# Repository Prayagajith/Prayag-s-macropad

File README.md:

# Prayag's Macropad
### My wonderful macropad that can be used for anything like video editting, 3d modeling, and maybe even for streaming

BOM:
- 12x Cherry MX Switches
- 12x 1N4148 Diodes
- 1x SK6812 MINI Led
- 1x EC11 Rotary Encoder 
- 1x XIAO RP2040
- 12x Blank DSA Keycaps
- 4x M3x16 Bolt
- 4x M3 Heatset

Schematic            |  PCB         |   Case
:-------------------------:|:-------------------------:|:-------------------------:|
 |  | 

## Extra Stuff

Had no idea what I was doing at the start but learnt along the way and learning new interesting stuff is always fun so had a lot of fun designing this project even though it is simple

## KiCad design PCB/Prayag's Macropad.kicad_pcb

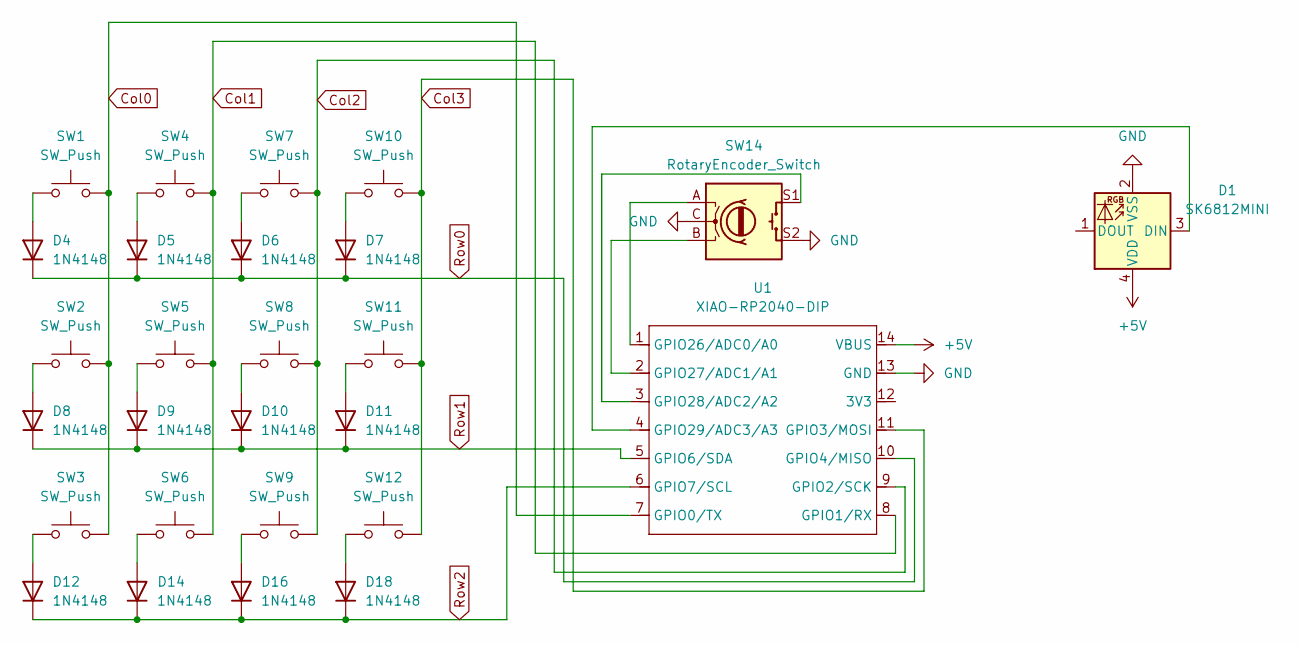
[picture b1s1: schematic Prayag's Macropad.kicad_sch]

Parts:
D1: SK6812MINI; LED_SK6812MINI_PLCC4_3.5x3.5mm_P1.75mm
D4, D5, D6, D7, D8, D9, D10, D11, D12, D14, D16, D18: 1N4148; D_DO-35_SOD27_P7.62mm_Horizontal
SW1, SW2, SW3, SW4, SW5, SW6, SW7, SW8, SW9, SW10, SW11, SW12: SW_Push; SW_Cherry_MX_1.00u_PCB
SW14: RotaryEncoder_Switch; RotaryEncoder_Alps_EC11E-Switch_Vertical_H20mm
U1: XIAO-RP2040-DIP

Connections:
+5V: D1.4 (VDD), U1.14 (VBUS)
Col0: SW1.2, SW2.2, SW3.2, U1.7 (GPIO0/TX)
Col1: SW4.1, SW5.1, SW6.1, U1.8 (GPIO1/RX)
Col2: SW7.1, SW8.1, SW9.1, U1.9 (GPIO2/SCK)
Col3: SW10.2, SW11.2, SW12.2, U1.11 (GPIO3/MOSI)
GND: D1.2 (VSS), SW14.C, SW14.S2, U1.13 (GND)
unnamed: D1.3 (DIN), U1.4 (GPIO29/ADC3/A3)
unnamed: D4.2 (A), SW1.1
unnamed: D5.2 (A), SW4.2
unnamed: D6.2 (A), SW7.2
unnamed: D7.2 (A), SW10.1
unnamed: D8.2 (A), SW2.1
unnamed: D9.2 (A), SW5.2
unnamed: D10.2 (A), SW8.2
unnamed: D11.2 (A), SW11.1
unnamed: D12.2 (A), SW3.1
unnamed: D14.2 (A), SW6.2
unnamed: D16.2 (A), SW9.2
unnamed: D18.2 (A), SW12.1
unnamed: SW14.A, U1.1 (GPIO26/ADC0/A0)
unnamed: SW14.B, U1.2 (GPIO27/ADC1/A1)
unnamed: SW14.S1, U1.3 (GPIO28/ADC2/A2)
Row0: D4.1 (K), D5.1 (K), D6.1 (K), D7.1 (K), U1.10 (GPIO4/MISO)
Row1: D8.1 (K), D9.1 (K), D10.1 (K), D11.1 (K), U1.5 (GPIO6/SDA)
Row2: D12.1 (K), D14.1 (K), D16.1 (K), D18.1 (K), U1.6 (GPIO7/SCL)

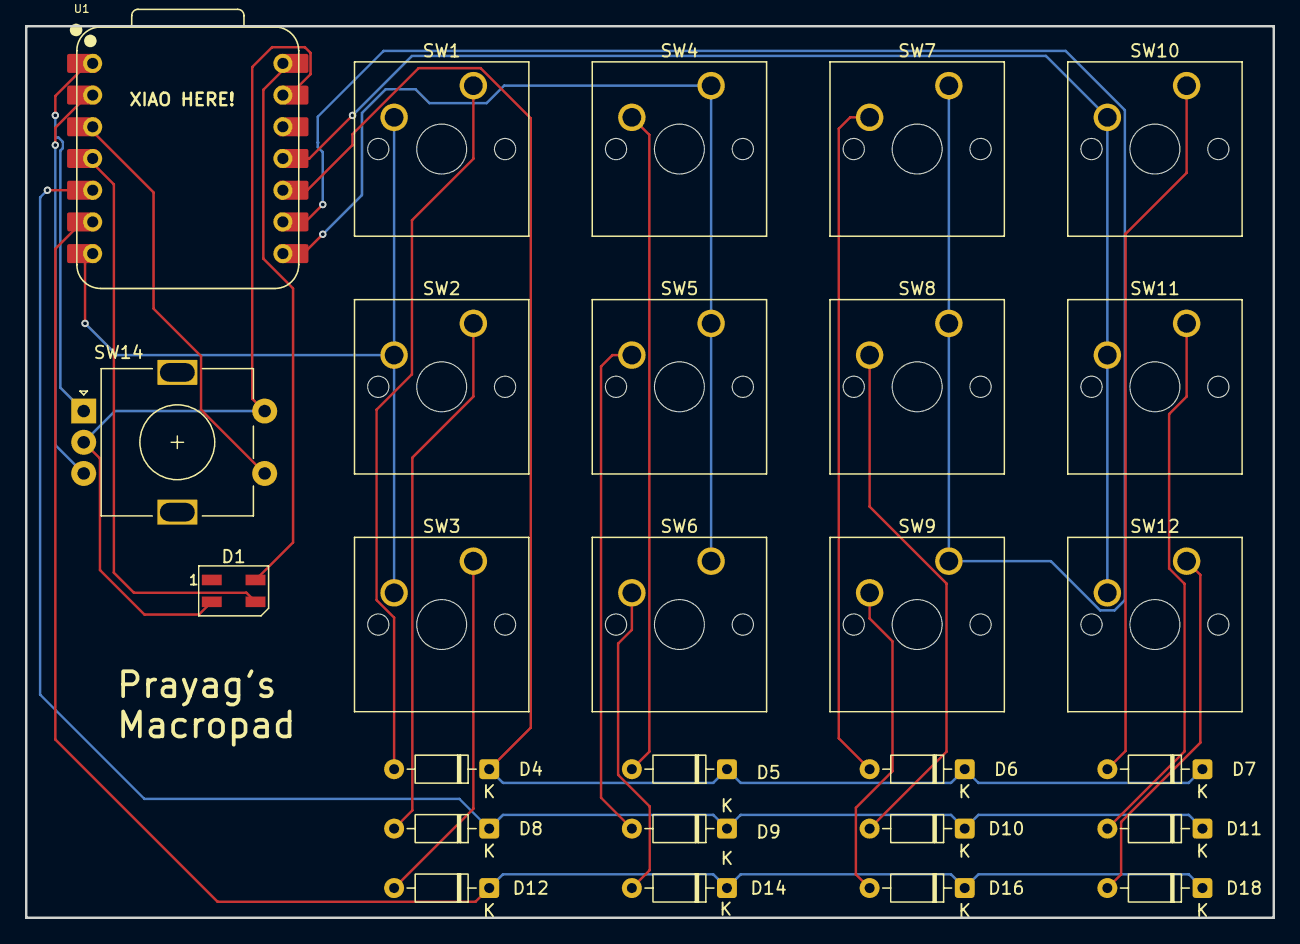
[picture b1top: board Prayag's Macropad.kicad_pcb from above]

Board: 2 copper layers, 100.0 x 71.4 mm, 27 parts (0 on the bottom side), 25 nets.

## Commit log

2025-12-27 name change
2025-12-28 pictures
2025-12-28 Fix image formatting in README.md
    Updated the image formatting in the README file.
2025-12-28 Convert image links to Markdown format
    Updated image links to Markdown format for better rendering.
2025-12-28 final readme
2025-12-28 final
2025-12-29 rewiew
2025-12-29 review
2025-12-30 Update README with new images and details
    Added new images and updated project description.
